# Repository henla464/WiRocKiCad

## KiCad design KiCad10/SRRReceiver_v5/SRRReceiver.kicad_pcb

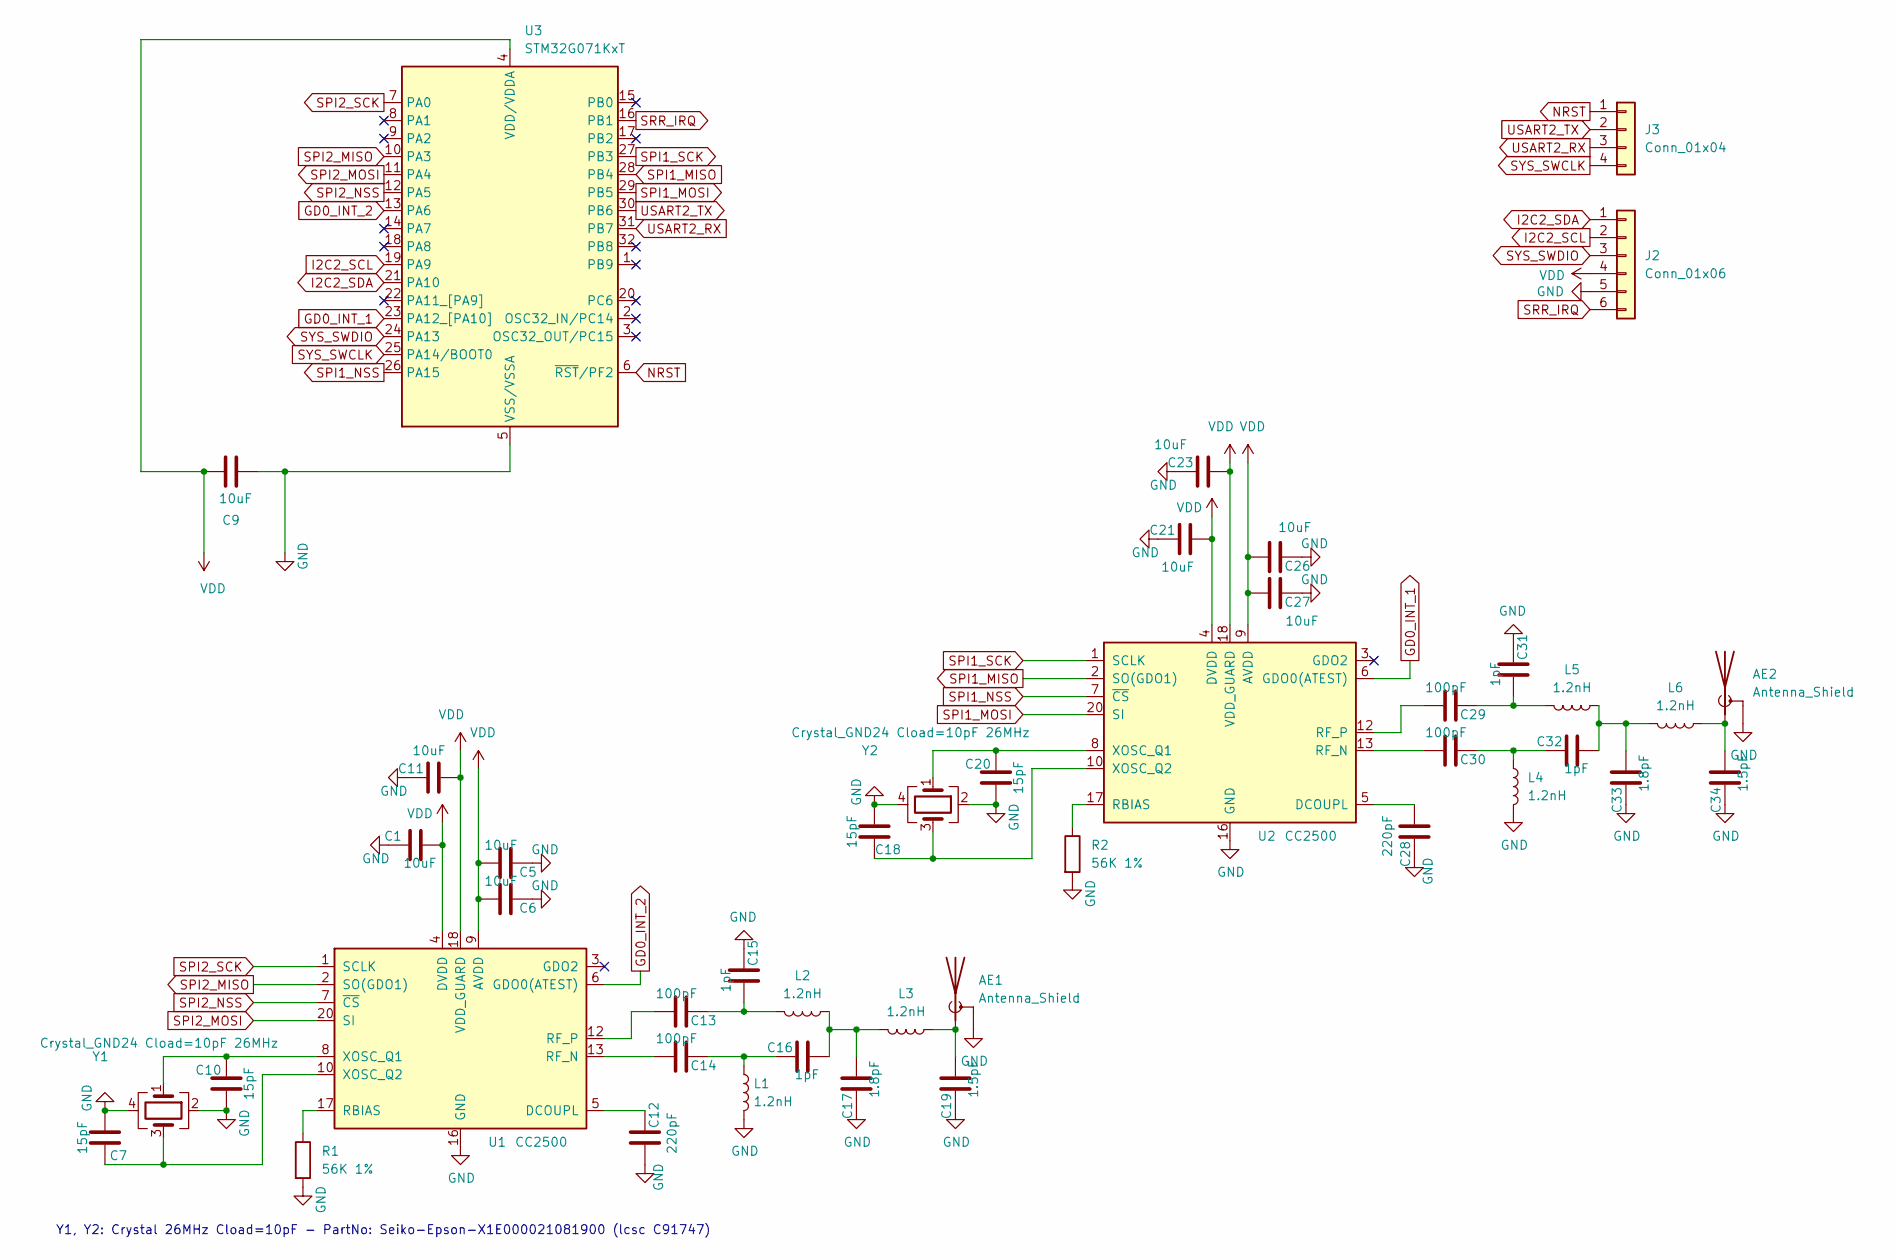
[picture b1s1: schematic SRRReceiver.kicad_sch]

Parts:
AE1, AE2: Antenna_Shield; Texas_SWRA117D_2.4GHz_Right-TunedForWiroc
C1, C5, C6, C11, C21, C23, C26, C27: 10uF; C_0402_1005Metric; LCSC C15525
C7, C10, C18, C20: 15pF; C_0402_1005Metric; LCSC C1548
C9: 10uF; C_0402_1005Metric_Pad0.74x0.62mm_HandSolder; LCSC C15525
C12, C28: 220pF; C_0402_1005Metric; LCSC C16772
C13, C14, C29, C30: 100pF; C_0402_1005Metric; LCSC C1546
C15, C16, C31, C32: 1pF; C_0402_1005Metric; LCSC C1550
C17, C33: 1.8pF; C_0402_1005Metric; LCSC C76902
C19, C34: 1.5pF; C_0402_1005Metric; LCSC C282238
J2: Conn_01x06; PinSocket_1x06_P1.27mm_Vertical
J3: Conn_01x04; PinSocket_1x04_P1.27mm_Vertical
L1, L2, L3, L4, L5, L6: 1.2nH; L_0402_1005Metric; LCSC C445745
R1, R2: 56K 1%; R_0402_1005Metric; LCSC C25796
U1, U2: CC2500; Texas_S-PVQFN-N20_EP2.4x2.4mm; LCSC C57494
U3: STM32G071KxT; LQFP-32_7x7mm_P0.8mm; LCSC C529339
Y1, Y2: Crystal_GND24 Cload=10pF 26MHz; Crystal_SMD_3225-4Pin_3.2x2.5mm; LCSC C91747

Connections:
GD0_INT_1: U2.6 (GDO0(ATEST)), U3.23 (PA12_[PA10])
GD0_INT_2: U1.6 (GDO0(ATEST)), U3.13 (PA6)
GND: AE1.2 (Shield), AE2.2 (Shield), C1.1, C5.1, C6.1, C7.1, C9.1, C10.1, C11.1, C12.2, C15.1, C17.1, C18.1, C19.1, C20.1, C21.1, C23.1, C26.1, C27.1, C28.1, C31.1, C33.1, C34.1, J2.5, L1.2, L4.2, R1.2, R2.2, U1.16 (GND), U1.19 (GND), U1.21 (GND), U2.16 (GND), U2.19 (GND), U2.21 (GND), U3.5 (VSS/VSSA), Y1.2, Y1.4, Y2.2, Y2.4
I2C2_SCL: J2.2, U3.19 (PA9)
I2C2_SDA: J2.1, U3.21 (PA10)
NRST: J3.1, U3.6 (~RST/PF2)
unnamed: AE1.1 (A), C19.2, L3.1
unnamed: AE2.1 (A), C34.2, L6.1
unnamed: C13.1, C15.2, L2.2
unnamed: C14.1, C16.1, L1.1
unnamed: C16.2, C17.2, L2.1, L3.2
unnamed: C29.1, C31.2, L5.2
unnamed: C30.1, C32.1, L4.1
unnamed: C32.2, C33.2, L5.1, L6.2
unnamed: C12.1, U1.5 (DCOUPL)
unnamed: R1.1, U1.17 (RBIAS)
unnamed: C14.2, U1.13 (RF_N)
unnamed: C13.2, U1.12 (RF_P)
unnamed: C10.2, U1.8 (XOSC_Q1), Y1.1
unnamed: C7.2, U1.10 (XOSC_Q2), Y1.3
unnamed: C28.2, U2.5 (DCOUPL)
unnamed: R2.1, U2.17 (RBIAS)
unnamed: C30.2, U2.13 (RF_N)
unnamed: C29.2, U2.12 (RF_P)
unnamed: C20.2, U2.8 (XOSC_Q1), Y2.1
unnamed: C18.2, U2.10 (XOSC_Q2), Y2.3
SPI1_MISO: U2.2 (SO(GDO1)), U3.28 (PB4)
SPI1_MOSI: U2.20 (SI), U3.29 (PB5)
SPI1_NSS: U2.7 (~CS), U3.26 (PA15)
SPI1_SCK: U2.1 (SCLK), U3.27 (PB3)
SPI2_MISO: U1.2 (SO(GDO1)), U3.10 (PA3)
SPI2_MOSI: U1.20 (SI), U3.11 (PA4)
SPI2_NSS: U1.7 (~CS), U3.12 (PA5)
SPI2_SCK: U1.1 (SCLK), U3.7 (PA0)
SRR_IRQ: J2.6, U3.16 (PB1)
SYS_SWCLK: J3.4, U3.25 (PA14/BOOT0)
SYS_SWDIO: J2.3, U3.24 (PA13)
USART2_RX: J3.3, U3.31 (PB7)
USART2_TX: J3.2, U3.30 (PB6)
VDD: C1.2, C5.2, C6.2, C9.2, C11.2, C21.2, C23.2, C26.2, C27.2, J2.4, U1.4 (DVDD), U1.9 (AVDD), U1.11 (AVDD), U1.14 (AVDD), U1.15 (AVDD), U1.18 (VDD_GUARD), U2.4 (DVDD), U2.9 (AVDD), U2.11 (AVDD), U2.14 (AVDD), U2.15 (AVDD), U2.18 (VDD_GUARD), U3.4 (VDD/VDDA)

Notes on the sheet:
Y1, Y2: Crystal 26MHz Cload=10pF - PartNo: Seiko-Epson-X1E000021081900 (lcsc C91747)

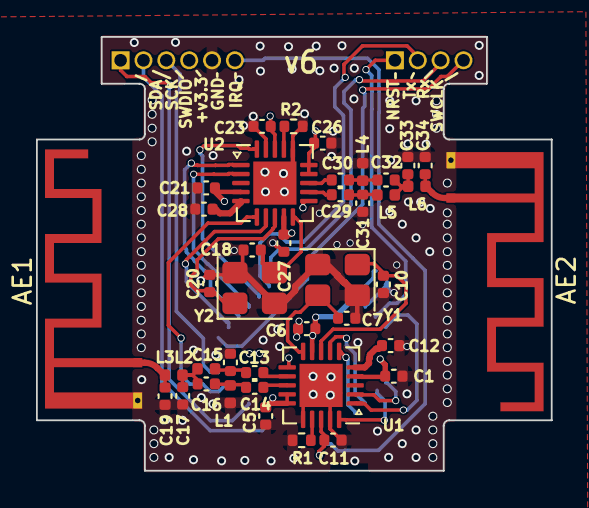
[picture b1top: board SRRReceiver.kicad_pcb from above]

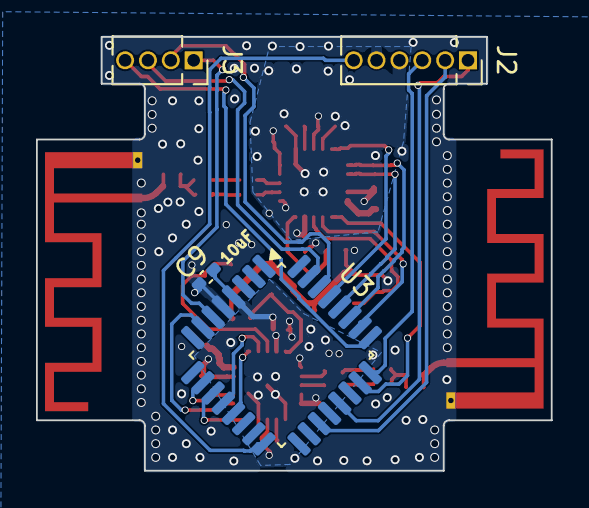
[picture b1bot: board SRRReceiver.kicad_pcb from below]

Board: 4 copper layers, 28.6 x 24.1 mm, 44 parts (4 on the bottom side), 40 nets.

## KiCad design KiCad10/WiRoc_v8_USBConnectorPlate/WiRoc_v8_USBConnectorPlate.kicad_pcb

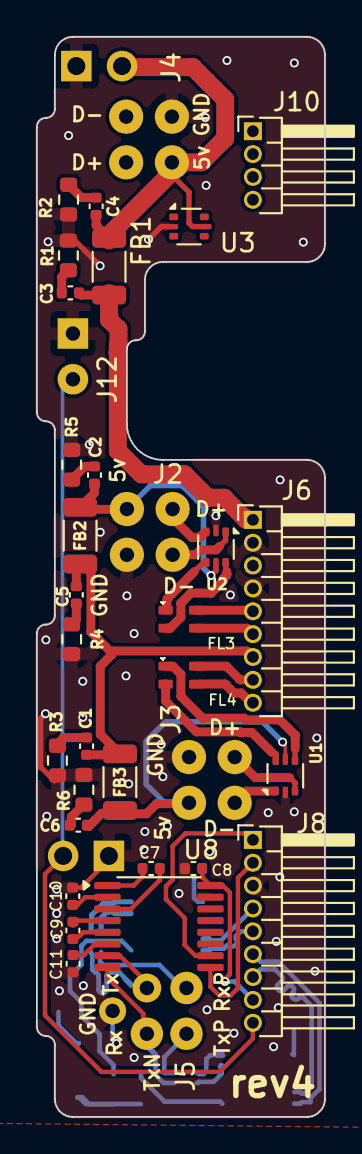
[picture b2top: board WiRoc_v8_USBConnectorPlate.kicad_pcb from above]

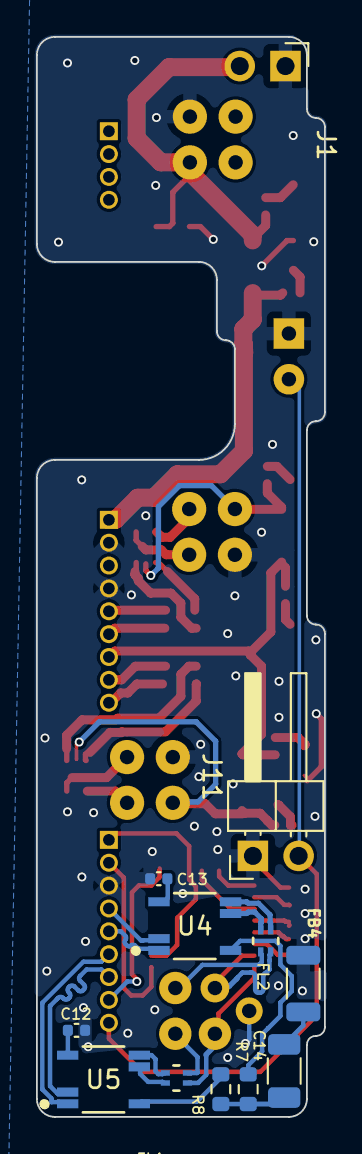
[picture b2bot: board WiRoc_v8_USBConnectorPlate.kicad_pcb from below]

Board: 2 copper layers, 16.0 x 60.0 mm, 48 parts (14 on the bottom side), 54 nets.

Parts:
C1, C2, C3, C4, C5, C6: 4.7 uF; C_0402_1005Metric
C7, C8, C9, C10, C11, C12, C13: 100 nF; C_0402_1005Metric
C14: 1 nF 2kV; C_1206_3216Metric
FB1, FB2, FB3, FB4: FerriteBead; L_1206_3216Metric
FL1, FL2: MCZ1210AH900L2TA0G; MCZ1210AH_L2_TDK
FL3, FL4: Choke_CommonMode_FerriteCore_1423; 0805_CommonModeChoke_1423
J1, J11: Conn_01x02; PinHeader_1x02_P2.54mm_Horizontal
J2: USB_Host_Data_02x02; USBConnPads7
J3: USB_Host_Data_02x02; USBConnPads8
J4: USB_Power_02x02; USBConnPads7
J5: Conn_01x05; SerialAndEthConnPads4Pin
J6, J8: Conn_01x09; PinHeader_1x09_P1.27mm_Horizontal
J10: Conn_01x04; PinHeader_1x04_P1.27mm_Horizontal
J12: Conn_01x02; PwrBtnPads
NT1, NT2: NetTie_2; NetTie-2_SMD_Pad0.3mm
R1, R2, R3, R4, R5, R6: 4.7 Ohm; R_0603_1608Metric
R7, R8: 75 Ohm; R_0603_1608Metric
U1, U2, U3: USBLC6-2P6; SOT-666
U4, U5: ALT4532M-170-T001; ALT4532M_TDK
U8: SP3232ECY-L; TSSOP-16_4.4x5mm_P0.65mm_PartOfSilkscreenRemoved

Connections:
/ETH-RXN: FL1.2, U5.5
/ETH-RXP: FL1.1, U5.4
/ETH-TXN: FL2.2, U4.5
/ETH-TXP: FL2.1, U4.4
/USB1-DM-ToESD: FL3.2, U2.6 (I/O1)
/USB1-DM-ToPad: J2.2, U2.1 (I/O1)
/USB1-DP-ToESD: FL3.1, U2.4 (I/O2)
/USB1-DP-ToPad: J2.3, U2.3 (I/O2)
/USB2-DM-ToESD: FL4.2, U1.6 (I/O1)
/USB2-DM-ToPad: J3.2, U1.1 (I/O1)
/USB2-DP-ToESD: FL4.1, U1.4 (I/O2)
/USB2-DP-ToPad: J3.3, U1.3 (I/O2)
CABLE-RXN: FL2.4, NT2.1
CABLE-RXP: FL2.3, J5.5
CABLE-TXN: FL1.3, NT1.1
CABLE-TXP: FL1.4, J5.4
EPHY-RXN: J8.5, U4.1
EPHY-RXP: J8.4, U4.2
EPHY-TXN: J8.7, U5.2
EPHY-TXP: J8.6, U5.1
GND: C8.1, C10.1, C11.1, C12.1, C13.1, FB4.1, J1.1, J2.4, J3.4, J4.4, J5.3, J6.2, J6.4, J8.3, J11.1, J12.1, R1.2, R2.2, R3.2, R4.2, R5.2, R6.2, U1.2 (GND), U2.2 (GND), U3.2 (GND), U8.15 (GND)
unnamed: C1.2, R3.1
unnamed: C2.2, R5.1
unnamed: C3.1, R1.1
unnamed: C4.2, R2.1
unnamed: C5.2, R4.1
unnamed: C6.2, R6.1
unnamed: C12.2, U5.3
unnamed: C13.2, U4.3
unnamed: C14.1, R7.2, R8.2
unnamed: C14.2, FB4.2
unnamed: R7.1, U4.6
unnamed: R8.1, U5.6
unnamed: C7.1, U8.1 (C1+)
unnamed: C7.2, U8.3 (C1-)
unnamed: C9.1, U8.4 (C2+)
unnamed: C9.2, U8.5 (C2-)
unnamed: C10.2, U8.2 (VS+)
unnamed: C11.2, U8.6 (VS-)
PWRBTN: J8.9, J11.2, J12.2
R2IN: J8.2, U8.9 (R2OUT)
SYS_3.3V: C8.2, J8.8, U8.16 (VCC)
T2OUT: J8.1, U8.10 (T2IN)
UART2_RX: J5.1, NT1.2, U8.8 (R2IN)
UART2_TX: J5.2, NT2.2, U8.7 (T2OUT)
USBHost-DM1: FL3.3, J6.6
USBHost-DM2: FL4.3, J6.9
USBHost-DP1: FL3.4, J6.5
USBHost-DP2: FL4.4, J6.8
VBUS: C3.2, FB1.2, J6.1
VBUS_IN: C4.1, FB1.1, J1.2, J4.1, U3.5 (VBUS)
VDD_5V: C1.1, C5.1, FB2.2, FB3.2, J6.7
VDD_5V_OUT1: C2.1, FB2.1, J2.1, U2.5 (VBUS)
VDD_5V_OUT2: C6.1, FB3.1, J3.1, U1.5 (VBUS)

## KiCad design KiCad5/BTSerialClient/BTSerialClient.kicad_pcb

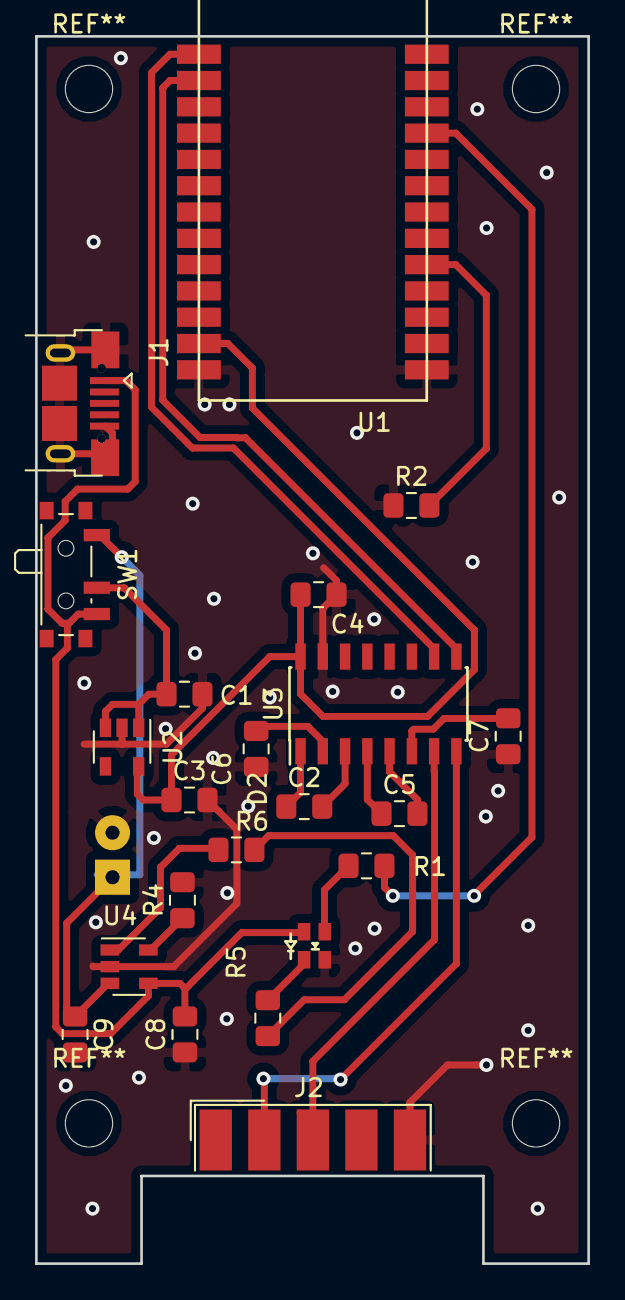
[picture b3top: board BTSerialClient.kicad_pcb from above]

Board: 2 copper layers, 31.5 x 70.0 mm, 23 parts (1 on the bottom side), 22 nets.

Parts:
BT1: Battery_Cell; JST_2.56
C1, C3: 1uF; C_0805_2012Metric_Pad1.15x1.40mm_HandSolder
C2, C4, C5, C6, C7: 100nF; C_0805_2012Metric_Pad1.15x1.40mm_HandSolder
C8, C9: 10uF; C_0805_2012Metric_Pad1.15x1.40mm_HandSolder
D2: LED_DUAL_ACCA; LED_Dual_1.7_1.6
J1: USB_B_Micro; USB_Micro-B_Horizontal
J2: DB9_Male; DSUB-9_Male_EdgeMount_P2.77mm
R1, R5, R6: 470; R_0805_2012Metric_Pad1.15x1.40mm_HandSolder
R2: 7.5K; R_0805_2012Metric_Pad1.15x1.40mm_HandSolder
R4: 2K; R_0805_2012Metric_Pad1.15x1.40mm_HandSolder
SW1: SW_SPDT; SW_SPDT_PCM12
U1: HC-02
U2: LN1134A332MR-G; SOT-23-5
U3: SP3232EEN; SOIC-16_3.9x9.9mm_P1.27mm
U4: LP4054HB5F; SOT-23-5

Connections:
3_3V: C3.1, C4.2, U1.12, U2.5, U3.16
BatteryPower: BT1.1, C9.1, SW1.1, U4.3
CEN: R6.1, U4.1
GND: BT1.2, C1.2, C3.2, C4.1, C6.1, C7.1, C8.1, C9.2, D2.2, J1.5, J1.6, J2.5, R2.1, R4.2, U1.13, U1.14, U2.2, U3.15, U4.2
LED: R1.2, U1.23
unnamed: C2.1, U3.1
unnamed: C2.2, U3.3
unnamed: C5.1, U3.4
unnamed: C5.2, U3.5
unnamed: C6.2, U3.2
unnamed: C7.2, U3.6
unnamed: D2.1, R1.1
unnamed: D2.3, R5.2
unnamed: J2.2, U3.8
unnamed: J2.3, U3.7
unnamed: R2.2, U1.18
unnamed: R4.1, U4.5
unnamed: R5.1, R6.2
unnamed: U1.1, U3.10
unnamed: U1.2, U3.9
SelectedPower: C1.1, SW1.2, U2.1, U2.3
VBUS: C8.2, D2.4, J1.1, SW1.3, U4.4

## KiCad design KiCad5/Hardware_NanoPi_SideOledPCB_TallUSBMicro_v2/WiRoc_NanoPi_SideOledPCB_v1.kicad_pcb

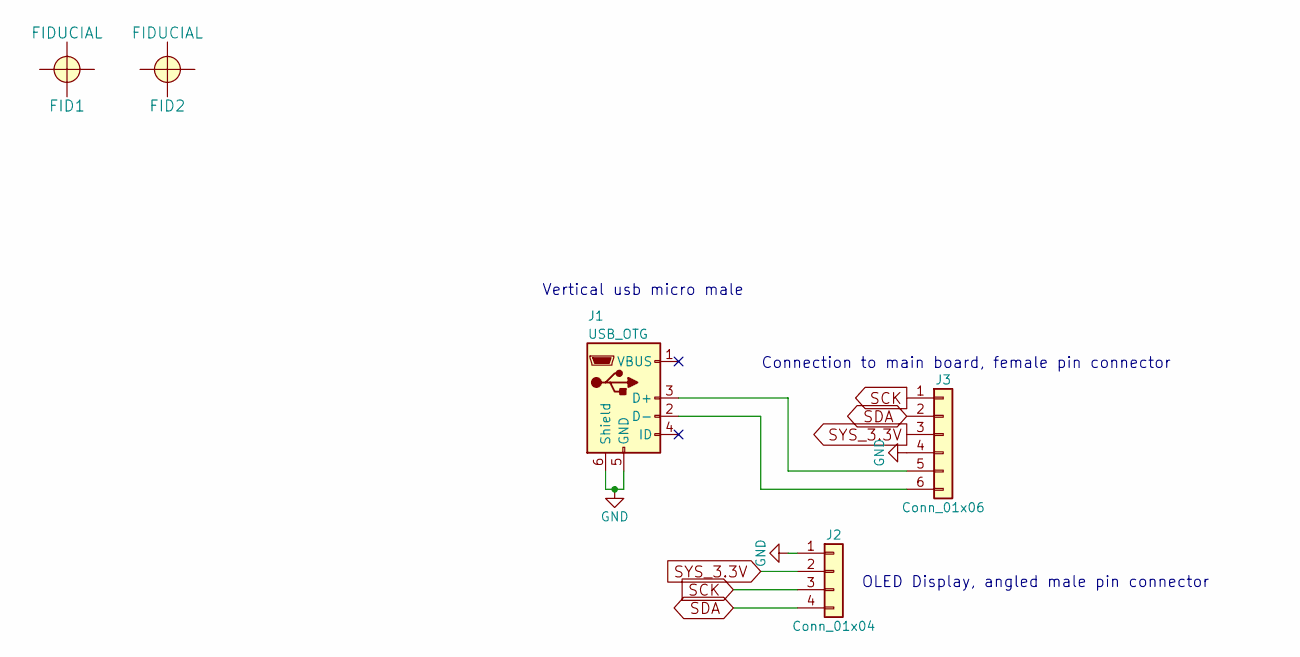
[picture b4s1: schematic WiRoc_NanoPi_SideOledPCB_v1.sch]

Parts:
FID1, FID2: FIDUCIAL; Fiducial
J1: USB_OTG; Vertical_USB_micro
J2: Conn_01x04; Pin_Header_Angled_1x04_Pitch2.54mm
J3: Conn_01x06; Socket_Strip_Straight_1x06_Pitch2.54mm

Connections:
GND: J1.5 (GND), J1.6 (Shield), J2.1, J3.4
unnamed: J1.2 (D-), J3.6
unnamed: J1.3 (D+), J3.5
SCK: J2.3, J3.1
SDA: J2.4, J3.2
SYS_3.3V: J2.2, J3.3

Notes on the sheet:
OLED Display, angled male pin connector
Connection to main board, female pin connector
Vertical usb micro male

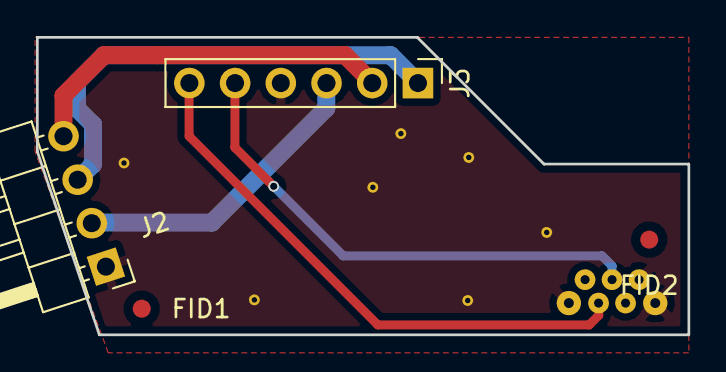
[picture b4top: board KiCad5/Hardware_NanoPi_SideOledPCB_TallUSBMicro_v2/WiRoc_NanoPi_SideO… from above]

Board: 2 copper layers, 36.2 x 16.5 mm, 5 parts (1 on the bottom side), 6 nets.

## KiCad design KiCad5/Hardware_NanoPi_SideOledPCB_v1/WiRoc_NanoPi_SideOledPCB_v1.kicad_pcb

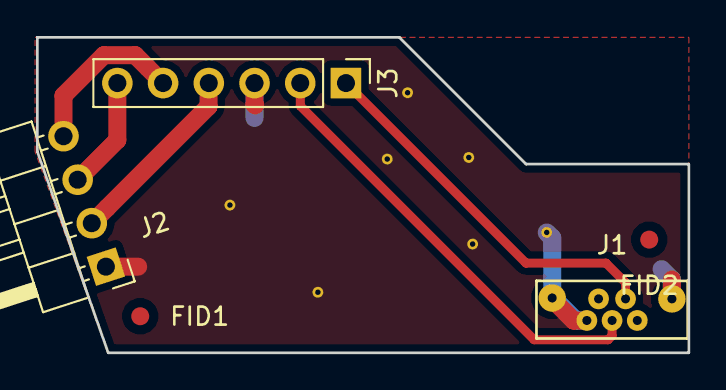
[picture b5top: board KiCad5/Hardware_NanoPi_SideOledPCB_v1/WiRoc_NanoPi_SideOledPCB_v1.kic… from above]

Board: 2 copper layers, 36.2 x 17.5 mm, 5 parts (0 on the bottom side), 6 nets.

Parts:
FID1, FID2: FIDUCIAL; Fiducial
J1: USB_OTG; micro-usb-super-short
J2: Conn_01x04; Pin_Header_Angled_1x04_Pitch2.54mm
J3: Conn_01x06; Socket_Strip_Straight_1x06_Pitch2.54mm

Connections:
GND: J1.5, J1.6, J2.1, J3.3
unnamed: J1.2, J3.1
unnamed: J1.3, J3.2
SCK: J2.3, J3.6
SDA: J2.4, J3.5
SYS_3.3V: J2.2, J3.4
